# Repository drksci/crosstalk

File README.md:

# delaytensor

Two attempts to compute with delay lines, simulated and benched.

**Delay Tensor** treats a bundle of coupled transmission lines as a fixed reservoir in front of a linear readout. Its one clear win, temporal XOR (0.724 raw, 0.995 reservoir), turned out under ablation to belong to the per-slot tanh, not the coupling. The recurrence matches ngspice to 5.27e-16.

**DLNN** trains ternary {-1, 0, +1} weights into the taps of an LC delay line, so the board's pick-and-place file is the model. It scores 0.878 on the simulated board line and 0.17 on the board as first drawn, until a gain bug is fixed, with a 0.6-point spread over 1,000 simulated boards.

Nothing here has been fabricated or measured. Every page says which of simulated, emulated, designed or pending applies. The experiments, tests and run data were produced by Claude Code sessions, mostly on the Fable model, under the author's direction.

## Read

| Start with | For |
|---|---|
| [docs/story.md](docs/story.md) | how the project got here: mainline and waypoints |
| [docs/architecture.md](docs/architecture.md) | both halves, the benches and the data flow on one page |
| [docs/design/](docs/design) | detailed design: [delay-tensor](docs/design/delay-tensor.md), [benches](docs/design/benches.md), [dlnn](docs/design/dlnn.md) |
| [AGENTS.md](AGENTS.md) · [llms.txt](llms.txt) | working here as an agent |

## Layout

```text
packages/delay-tensor/   reservoir simulation, readouts, experiments, CLI (uv workspace member)
benches/                 ngspice equivalence, RLCG lines, transient, scikit-rf, ERA extraction
packages/dlnn/           ternary tapped-delay-line network, tiers V/E/C/P, board-as-code (own venv)
packages/dlnn-paper/     notebooks, article draft, board renders, claim checker
docs/                    story, architecture, design docs, figures
```

## Quick start: Delay Tensor

```bash
uv sync --all-packages
uv run --all-packages delay-tensor classify --config packages/delay-tensor/configs/tensor_8x64.yaml --seeds 1234,1235,1236
uv run --all-packages delay-tensor xor --config packages/delay-tensor/configs/tensor_8x64.yaml
uv run --all-packages delay-tensor mnist --config packages/delay-tensor/configs/mnist_8x784.yaml
uv run --all-packages pytest
```

Each run writes `results/<run_id>/` with `report.html`, `metrics.json`, `runs.csv`, `observations.txt` and the exact `config.yaml`. MNIST takes a few minutes; features go to a float32 memmap, not RAM. The benches need the optional group: `uv sync --all-packages --group bench`, with ngspice reachable through `NGSPICE_LIBRARY_PATH`.

| Experiment (3 seeds) | Raw | Tensor | Delta |
|---|---|---|---|
| Six-way classification | 0.847 ± 0.016 | 0.861 ± 0.022 | +0.014 ± 0.006 |
| Temporal XOR | 0.724 ± 0.024 | 0.995 ± 0.009 | +0.271 ± 0.024 |
| MNIST | 0.9136 ± 0.0003 | 0.9146 ± 0.0012 | +0.0011 ± 0.0014 |

## Quick start: DLNN

```bash
cd packages/dlnn
./setup.sh                      # WITH_LLM=0 skips the optional local LLM build
.venv/bin/python -m pytest -q   # torch-dependent tests skip without the train extra
```

Full commands and versions: [packages/dlnn/docs/reproducibility.md](packages/dlnn/docs/reproducibility.md). The verify notebook `packages/dlnn-paper/notebooks/00_verify.ipynb` re-checks every printed number against its data.

## Archive

The original June 2026 `phase-lattice-sim` workspace lives outside this repository, with its own history, and is kept as a reference only.

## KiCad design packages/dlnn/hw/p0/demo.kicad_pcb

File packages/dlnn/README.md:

# DLNN: ternary delay-line neural network, four-fidelity simulation

A tapped coaxial delay-line network with ternary taps (tap polarity = BitNet-style {-1, 0, +1} weights) and a differential-pair tanh,
trained on synthetic modulation recognition and simulated at four fidelities (V ideal math, E fixed point + Verilog RTL, C ngspice circuit,
R scikit-rf RF channel), with a small local LLM that comments on the side-by-side results.

**Simulation only, synthetic data, no hardware measurement.** C and R are 16 to 20 points below V at the headline `--cascade` operating point
(32 dB/us loss, no repeaters). Two things cause that: the operating point is not buildable without repeaters, **and** C's default per-layer gain trim over-drives layer 3
(C scores 0.663 by default, 0.804 with no compensation, 0.805 with ideal per-tap repeaters at the same loss), so most of C's gap is a modelling choice, not line loss.
The numbers, the caveats and the failures are in the docs.

**Start here: [`docs/README.md`](docs/README.md)** (index, results, honesty page, reproducibility).

## Quickstart (commands run on this box: 4 cores, 15 GB, Ubuntu 24.04, Python 3.13)

```bash
./setup.sh                                  # idempotent; first run builds llama-cpp-python from source (~4 min, needs cmake + a C/C++ compiler)
.venv/bin/python run.py --task modrec --tiers V,E,C,R --cascade --llm qwen --db sqlite --out out --run-id final-w32   # about 13 min
.venv/bin/python run.py --task modrec --tiers V,E,C,R --cascade --llm none --model models/tdlnet_modrec_ternary.npz --run-id final-w8   # width-8 secondary, about 3 min
.venv/bin/python scripts/make_results_md.py # regenerate docs/results.md from out/final-w32 and out/final-w8
.venv/bin/python -m pytest -q               # test suite
```

Use `--llm none` for the template commentary (no Qwen, no GGUF needed; `WITH_LLM=0 ./setup.sh` skips the build and the 1.1 GB download).
Notebooks: `notebooks/00..06_*.ipynb` (executed; see `docs/notebooks.md`). Full list of commands and versions: `docs/reproducibility.md`.

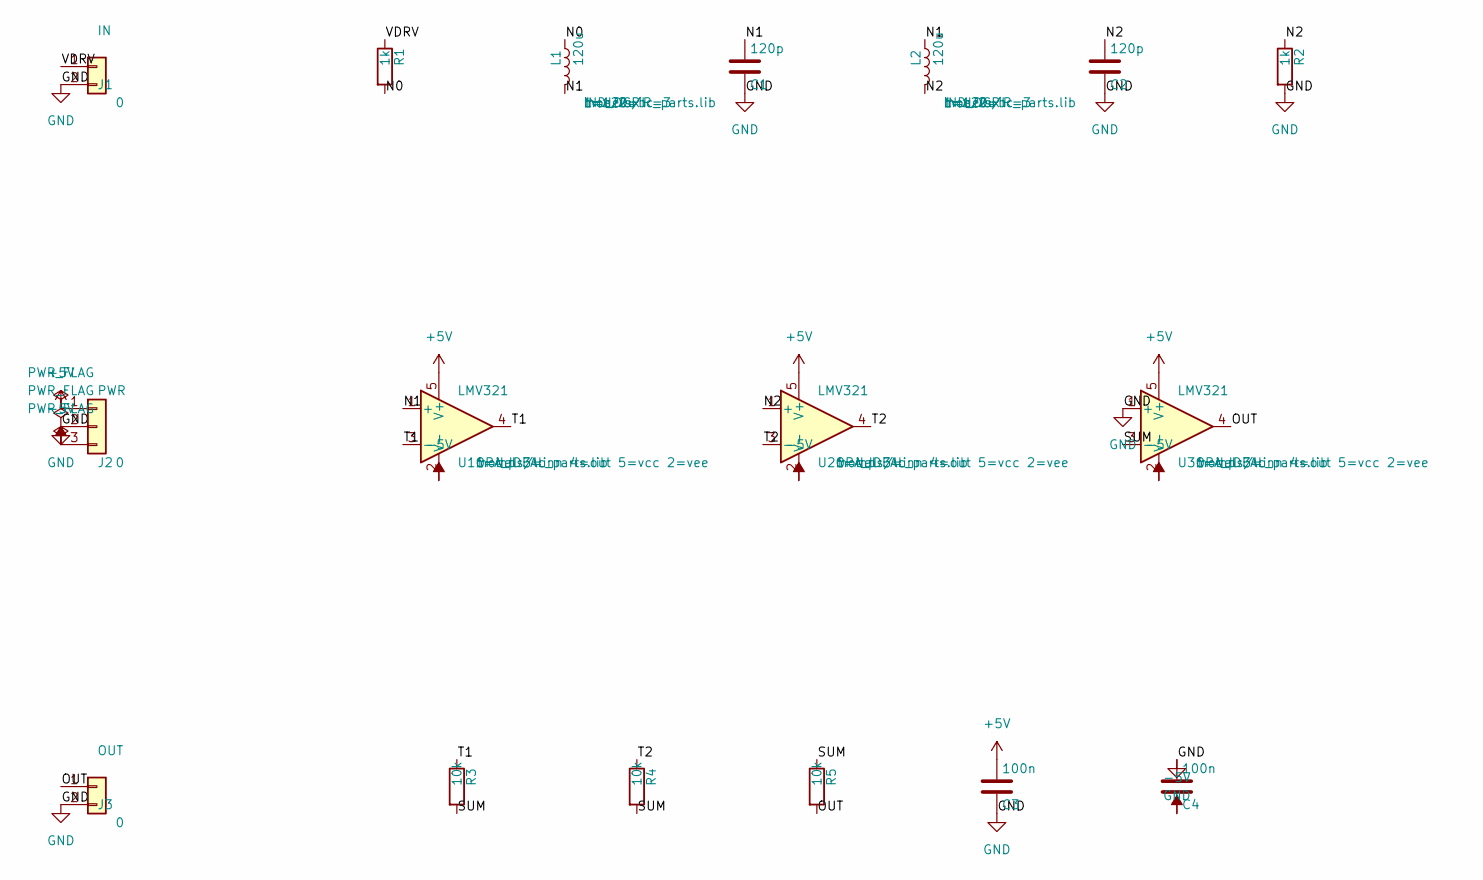
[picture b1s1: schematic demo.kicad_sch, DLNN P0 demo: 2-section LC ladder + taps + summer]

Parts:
C1, C2: 120p; C_0603_1608Metric
C3, C4: 100n; C_0603_1608Metric
J1: IN; PinHeader_1x02_P2.54mm_Vertical
J2: PWR; PinHeader_1x03_P2.54mm_Vertical
J3: OUT; PinHeader_1x02_P2.54mm_Vertical
L1, L2: 120u; L_1210_3225Metric
R1, R2: 1k; R_0603_1608Metric
R3, R4, R5: 10k; R_0603_1608Metric
U1, U2, U3: LMV321; SOT-23-5

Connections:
+5V: C3.1, J2.1, U1.5 (V+), U2.5 (V+), U3.5 (V+)
-5V: C4.2, J2.3, U1.2 (V-), U2.2 (V-), U3.2 (V-)
/N0: L1.1, R1.2
/N1: C1.1, L1.2, L2.1, U1.1 (+)
/N2: C2.1, L2.2, R2.1, U2.1 (+)
/OUT: J3.1, R5.2, U3.4
/SUM: R3.2, R4.2, R5.1, U3.3 (-)
/T1: R3.1, U1.3 (-), U1.4
/T2: R4.1, U2.3 (-), U2.4
/VDRV: J1.1, R1.1
GND: C1.2, C2.2, C3.2, C4.1, J1.2, J2.2, J3.2, R2.2, U3.1 (+)

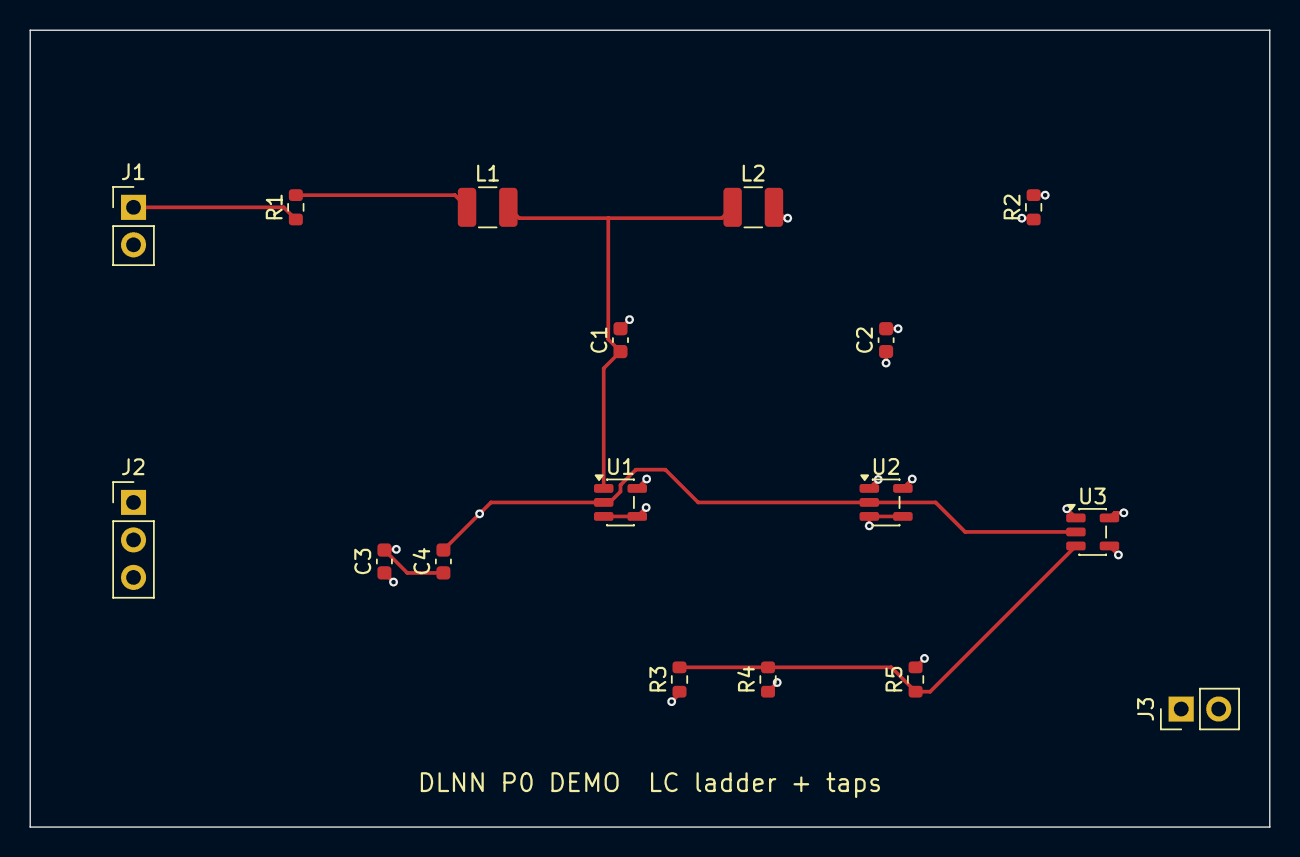
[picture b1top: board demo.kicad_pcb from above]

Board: 4 copper layers, 84.0 x 54.0 mm, 17 parts (0 on the bottom side), 11 nets.

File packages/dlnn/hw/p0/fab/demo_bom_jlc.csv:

Comment,Designator,Footprint,LCSC Part #
120p,"C1,C2",C_0603_1608Metric,
100n,"C3,C4",C_0603_1608Metric,C14663
120u,"L1,L2",L_1210_3225Metric,
1k,"R1,R2",R_0603_1608Metric,C21190
10k,"R3,R4,R5",R_0603_1608Metric,C25804
LMV321,"U1,U2,U3",SOT-23-5,

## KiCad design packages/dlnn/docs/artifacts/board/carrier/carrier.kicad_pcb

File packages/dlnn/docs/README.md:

# DLNN: a ternary delay-line neural network, simulated at four fidelities

**Simulation only. Synthetic data. No hardware was built or measured.** Read `honesty.md` before quoting any number.

## The concept in one paragraph

A tapped coaxial delay line with couplers and a combiner computes a convolution; making each tap one of {+1, 0, -1} (coupler, no coupler, coupler through a 180 degree hybrid)
is the ternary weight alphabet of BitNet b1.58, and a bipolar differential pair supplies a native tanh. Three such layers with dilations 1, 4 and 16, a time-average pool and a small
digital readout form a ternary dilated convolutional classifier (`TDL-Net`). This repository trains it offline (PyTorch, ternary QAT) on 8-class modulation recognition with synthetic
I/Q data, then evaluates the **same weights** at four fidelities: **V** ideal math, **E** 8-bit fixed point with Verilog RTL cross-check, **C** ngspice circuit (layer-1 unit cell plus a
circuit-calibrated model), **R** scikit-rf RF channel (loss, dispersion, couplers, noise, saturation). A small local LLM (Qwen2.5-1.5B) writes a number-checked commentary on the side-by-side
results; it is a commentator, not part of the network.

## Headline results

<!-- headline:begin -->
_Generated by `scripts/make_results_md.py` from `out/final-w32/compare.json` (width-32 ternary model, all four tiers on all 4000 test examples, `--cascade`)._

| tier | status | accuracy (4000 test examples) | top-1 agreement vs V |
|---|---|---|---|
| V | ok | 0.863 | 1.000 |
| E | ok | 0.863 | 0.997 |
| C | ok | 0.663 | 0.662 |
| R | ok | 0.701 | 0.709 |
| float32 reference | reference | 0.919 |  |
<!-- headline:end -->

Read this with care. C and R sit 16 to 20 points below V (V 0.863, R 0.701, C 0.663) for **two measured reasons that have to be kept apart**:

1. **The operating point is not buildable.** `--cascade` runs both tiers at the 32 dB per microsecond (RG-58) line loss with no repeaters (the longest layer-3 tap is about 36 dB down). At 0 dB/us they return to about V's level (`results.md`, section 2).
2. **C's default compensation mode over-drives layer 3, and that is most of C's gap.** At the same 32 dB/us, C scores 0.663 with its default `layer` mode (one ideal gain trim per layer), 0.804 with no compensation at all and 0.805 with ideal per-tap repeaters
   (`params/circuit_diagnostics.json`). So about 14 of C's 20 points belong to the per-layer gain-trim modelling choice and only about 6 to the line loss itself. The trim in layer 3 is 2.85x and multiplies the unattenuated short taps too: 72.8 % of C's layer-3 activations are in
   tanh saturation (|tanh| > 0.95), against 49.9 % in V, 31.1 % with no compensation and 50.1 % with per-tap repeaters (4000 test examples; `circuit_extraction.md`, "Where C's gap comes from"). R uses a similar per-layer gain rule and shows the same layer-3 saturation (71.7 %); with ideal per-tap
   equalisation R scores 0.810 instead of 0.701 at 32 dB/us. Whether R's rule is an artefact of the model or what a real amplifier chain would do was not decided.

The width-32 net is the headline; the plan's width-8 net misses its target and is reported next to it (`results.md`, section 4).

## How to run

```bash
./setup.sh                                                   # idempotent; builds llama-cpp-python from source the first time (~4 min)
.venv/bin/python run.py --task modrec --tiers V,E,C,R --cascade --llm none     # about 10 min on 4 cores, no LLM
.venv/bin/python run.py --task modrec --tiers V,E,C,R --cascade --llm qwen     # + Qwen commentary (about 3 min extra)
.venv/bin/python scripts/make_results_md.py --w32 out/<run_id> --w8 out/<w8_run_id>   # regenerate docs/results.md
.venv/bin/python -m dlnn.viz.export --run <run_id> --llm-run <run_id> --secondary <w8_run_id>   # figures -> docs/figures/
DLNN_RUN=out/<run_id> DLNN_LLM_RUN=out/<run_id> .venv/bin/jupyter nbconvert --to notebook --execute --inplace \
    --ExecutePreprocessor.kernel_name=dlnn --ExecutePreprocessor.timeout=900 notebooks/0*.ipynb
.venv/bin/python -m pytest -q
```

Exact commands, versions, hashes and timings of the final run: `reproducibility.md`. More options: `quickstart.md`.

## Map

| Doc | What it is |
|---|---|
| `concept_and_math.md` | layer equations, tap polarity to ternary mapping, tanh diff pair, signal encoding, physical limits, minimal hybrid, why this is a neural net and not an LLM |
| `architecture.md` | repo layout, data contract, tier interface, cascade, pipeline stages, block diagram, Postgres schema |
| `results.md` | generated tables and figures of the final run (`scripts/make_results_md.py`), sweeps, loss/cascade explanation, float vs ternary, w8 vs w32, RTL counts, LLM eval and the real commentary |
| `reproducibility.md` | versions, seeds, hashes, commands, runtimes, hardware |
| `honesty.md` | what is and is not claimed; known gaps; next steps |
| `review.md` | independent review of the documentation, with the response to every finding (M4d) |
| `deviations.md` | planned versus done, per milestone |
| `plan.md` | the original plan (with a banner) |
| `quickstart.md`, `tiers.md`, `contract.md`, `model_export.md`, `fixed_point_spec.md`, `circuit_extraction.md`, `rf_model.md`, `llm_commentary.md`, `llm_eval.md`, `notebooks.md` | component documents written during the milestones |
| `build-log.md`, `build-log-M1.md` ... `build-log-M4b.md` | what each milestone actually ran and measured |

### Notebooks (`notebooks/`, executed, outputs saved; see `notebooks.md`)

| Notebook | Content |
|---|---|
| `00_overview` | concept, tiers, headline table, figure 1 and 7 |
| `01_task_and_model` | the eight signal classes, dataset hash, training report, 8PSK collapse of width 8, weight histograms |
| `02_virtual` | ideal forward pass step by step |
| `03_emulated` | fixed point, ADC and LUT, live RTL vs numpy check |
| `04_circuit` | live ngspice `.dc`, `.ac`, `.tran`; SPICE vs calibrated vs extrapolated; loss compensation modes |
| `05_rf` | scikit-rf lines and tap paths, live sweeps on a subset |
| `06_compare_and_llm` | side-by-side matrix, figures 4-7, card text, commentary with flags |

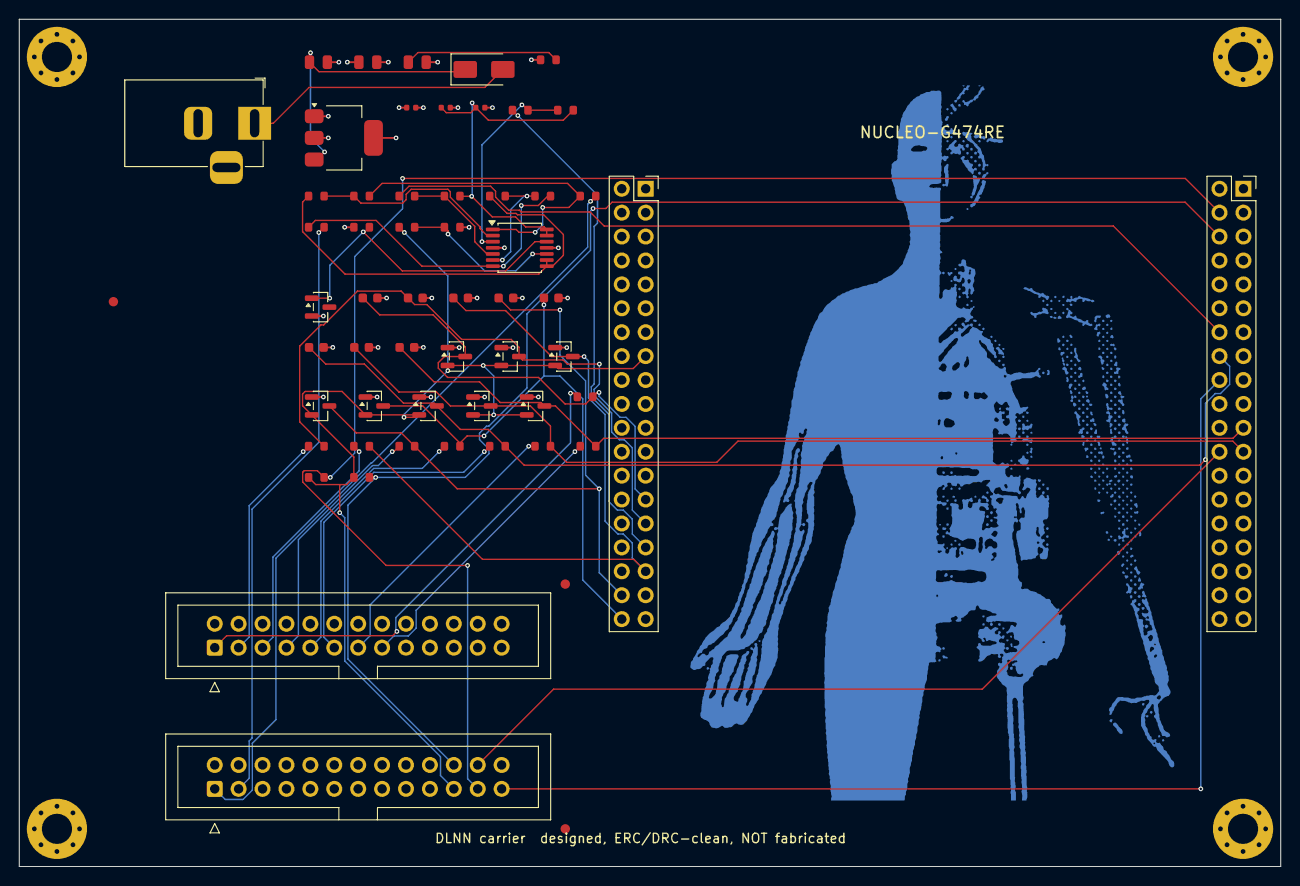
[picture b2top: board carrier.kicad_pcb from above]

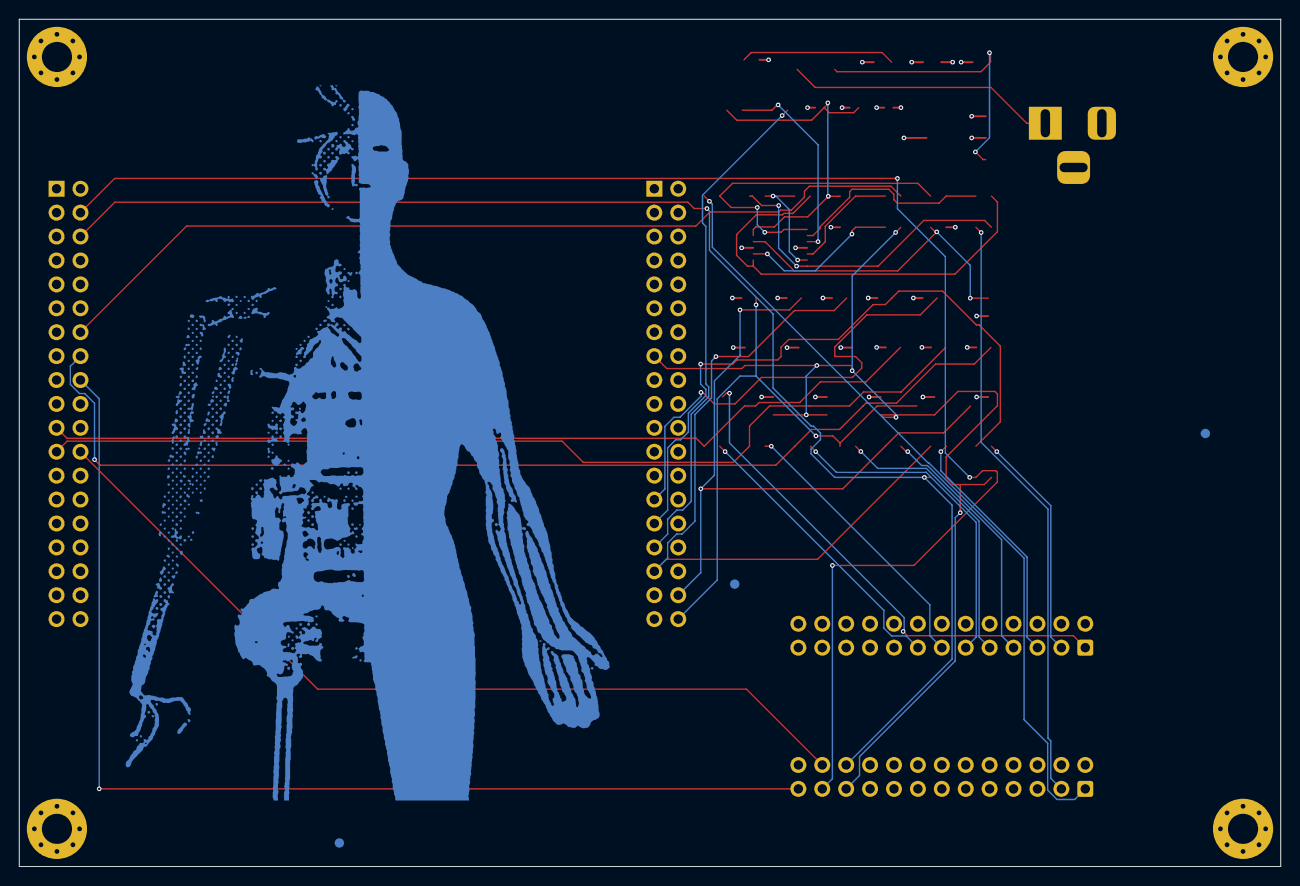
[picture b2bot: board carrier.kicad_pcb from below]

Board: 4 copper layers, 134.0 x 90.0 mm, 66 parts (4 on the bottom side), 40 nets.

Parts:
ART1: ART_carrier_gold
CAI0, CAI1, CAI2, CAI3, CAI4, CAI5, CAI6, CAI7: 330p; C_0603_1608Metric
CD1: 100n; C_0402_1005Metric
CDV0, CDV1: 100n; C_0402_1005Metric
CJ1, CJ2, CJ3: 10u; C_0805_2012Metric
CN7: CN7; PinSocket_2x19_P2.54mm_Vertical
CN10: CN10; PinSocket_2x19_P2.54mm_Vertical
D1: SS14; D_SMA
DAI0, DAI1, DAI2, DAI3, DAI4, DAI5, DAI6, DAI7: BAT54S; SOT-23
FID1, FID2, FID3, FID4, FID5, FID6: Fiducial_1mm_Mask2mm
H1, H2, H3, H4: MountingHole_3.2mm_M3_Pad_Via
J1: 7-9 V DC; BarrelJack_Horizontal
JADC1: 2x13 IDC; IDC-Header_2x13_P2.54mm_Vertical
JT1: 2x13 IDC; IDC-Header_2x13_P2.54mm_Vertical
RAI0, RAI1, RAI2, RAI3, RAI4, RAI5, RAI6, RAI7: 1k; R_0603_1608Metric
RDI01, RDI02, RDI03, RDI04, RDI11, RDI12, RDI13, RDI14: 10k; R_0603_1608Metric
RDO01, RDO11: 100; R_0603_1608Metric
RESR1: 1; R_0603_1608Metric
RPU1, RPU2: 4.7k; R_0603_1608Metric
RRF1: 2.49k; R_0603_1608Metric
RVA1, RVA2: 10k; R_0603_1608Metric
U1: AMS1117-5.0; SOT-223-3_TabPin2
UC1: TLV9064IPW; TSSOP-14_4.4x5mm_P0.65mm
UREF1: LM4040B25FTA; SOT-23

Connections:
+3V3: CN7.16, DAI0.2, DAI1.2, DAI2.2, DAI3.2, DAI4.2, DAI5.2, DAI6.2, DAI7.2, JT1.21, RPU1.1, RPU2.1, RVA1.1
+5VA: CD1.1, CJ2.1, JT1.17, JT1.19, RESR1.1, RRF1.1, U1.2, UC1.4
/dac/CO0: RDI04.2, RDO01.1, UC1.1
/dac/CO1: RDI14.2, RDO11.1, UC1.7
/dac/DN0: RDI03.2, RDI04.1, UC1.2
/dac/DN1: RDI13.2, RDI14.1, UC1.6
/dac/DP0: RDI01.2, RDI02.1, UC1.3
/dac/DP1: RDI11.2, RDI12.1, UC1.5
/dac/V2R5: RRF1.2, UC1.12, UREF1.1
/dac/V25: CDV0.1, CDV1.1, RDI02.2, RDI12.2, UC1.13, UC1.14
/dac/VAB: RDI03.1, RDI13.1, UC1.8, UC1.9
/dac/VAD: RVA1.2, RVA2.1, UC1.10
/power/ESR: CJ3.1, RESR1.2
/power/VJ0: D1.2, J1.1
/power/VJ1: CJ1.1, D1.1, U1.3
ADC0: CAI0.1, CN7.28, DAI0.3, RAI0.2
ADC1: CAI1.1, CN7.30, DAI1.3, RAI1.2
ADC2: CAI2.1, CN7.34, DAI2.3, RAI2.2
ADC3: CAI3.1, CN7.35, DAI3.3, RAI3.2
ADC4: CAI4.1, CN7.37, DAI4.3, RAI4.2
ADC5: CAI5.1, CN10.15, DAI5.3, RAI5.2
ADC6: CAI6.1, CN10.24, DAI6.3, RAI6.2
ADC7: CAI7.1, CN10.22, DAI7.3, RAI7.2
CSIG0: JT1.1, RDO01.2
CSIG1: JT1.3, RDO11.2
DAC_I: CN7.32, RDI01.1
DAC_Q: CN10.13, RDI11.1
GND: CAI0.2, CAI1.2, CAI2.2, CAI3.2, CAI4.2, CAI5.2, CAI6.2, CAI7.2, CD1.2, CDV0.2, CDV1.2, CJ1.2, CJ2.2, CJ3.2, CN7.8, CN7.19, CN7.20, CN7.22, CN10.9, CN10.20, DAI0.1, DAI1.1, DAI2.1, DAI3.1, DAI4.1, DAI5.1, DAI6.1, DAI7.1, H1.1, H2.1, H3.1, H4.1, J1.2, JADC1.2, JADC1.4, JADC1.6, JADC1.8, JADC1.10, JADC1.12, JADC1.14, JADC1.16, JADC1.18, JADC1.20, JADC1.26, JT1.2, JT1.4, JT1.6, JT1.8, JT1.10, JT1.12, JT1.14, JT1.16, JT1.18, JT1.20, JT1.26, RVA2.2, U1.1, UC1.11, UREF1.2
RO0: JADC1.1, RAI0.1
RO1: JADC1.3, RAI1.1
RO2: JADC1.5, RAI2.1
RO3: JADC1.7, RAI3.1
RO4: JADC1.9, RAI4.1
RO5: JADC1.11, RAI5.1
RO6: JADC1.13, RAI6.1
RO7: JADC1.15, RAI7.1
SCL: CN10.3, JT1.23, RPU1.2
SDA: CN10.5, JT1.22, RPU2.2
SH_CLK: CN10.23, JT1.24
SYNC: CN10.17, JT1.25
